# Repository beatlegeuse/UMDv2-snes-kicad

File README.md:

# UMDv2-snes-kicad
UMDv2 SNES Cartridge Adapter

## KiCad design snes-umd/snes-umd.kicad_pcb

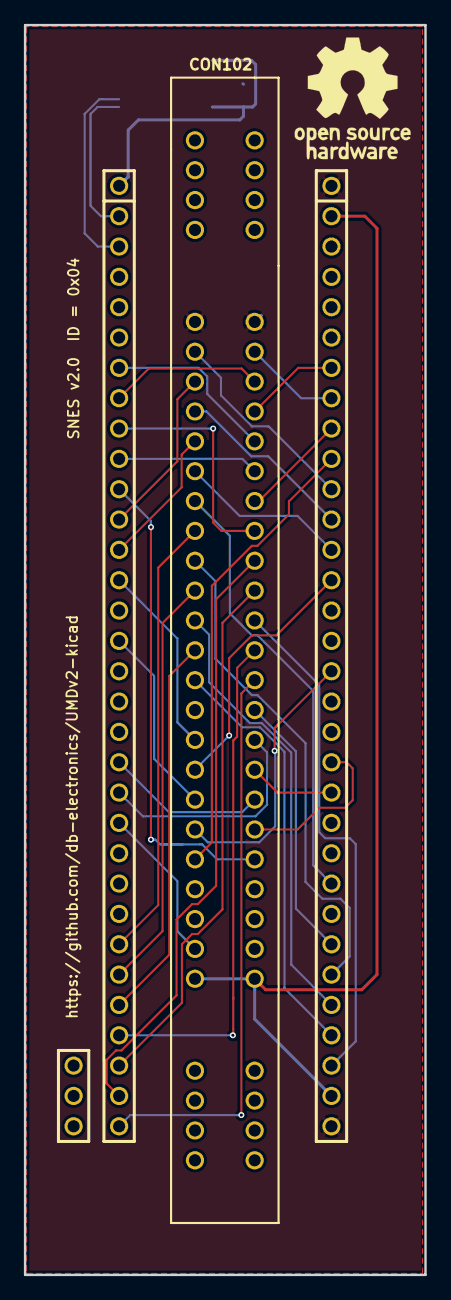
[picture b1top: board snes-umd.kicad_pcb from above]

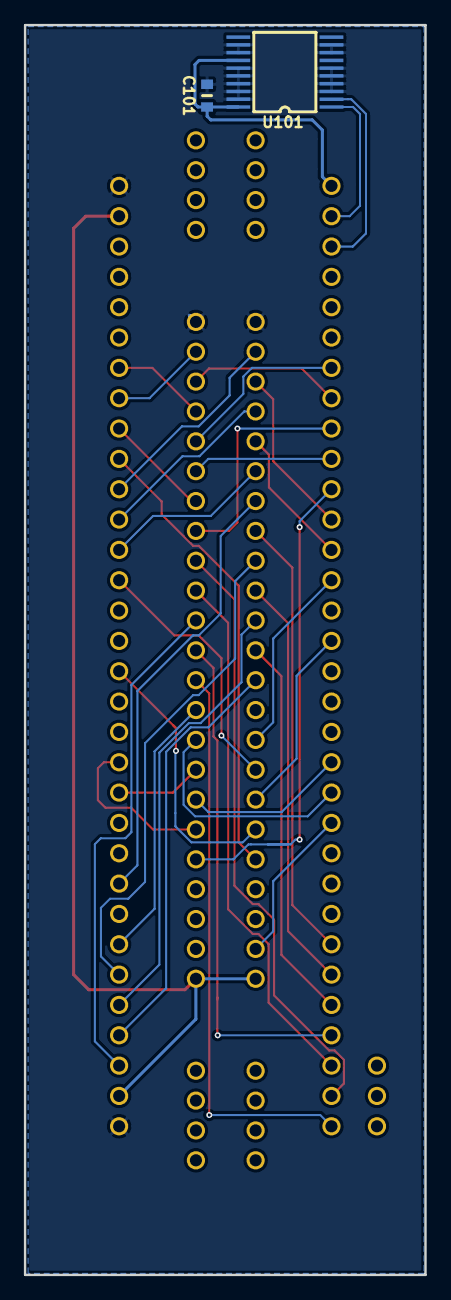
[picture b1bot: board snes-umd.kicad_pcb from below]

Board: 2 copper layers, 33.5 x 104.6 mm, 4 parts (2 on the bottom side), 41 nets.

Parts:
C101: 0.1uF/50V; 0603
CON101: UMDv2-CONN; UMD-CONN-DIP64
CON102: SNES-CONN; SNES-CONN-EXP
U101: MCP23008T-E_SS; SSOP-20

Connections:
+3V3: C101.1, CON101.1, U101.14, U101.20
+5V: CON101.34, CON101.63, CON102.27, CON102.58
/A0: CON101.36, CON102.17
/A1: CON101.28, CON102.16
/A2: CON101.37, CON102.15
/A3: CON101.27, CON102.14
/A4: CON101.38, CON102.13
/A5: CON101.26, CON102.12
/A6: CON101.41, CON102.11
/A7: CON101.52, CON102.10
/A8: CON101.13, CON102.9
/A9: CON101.53, CON102.8
/A10: CON101.12, CON102.7
/A11: CON101.54, CON102.6
/A12: CON101.57, CON102.37
/A13: CON101.8, CON102.38
/A14: CON101.58, CON102.39
/A15: CON101.7, CON102.40
/A16: CON101.10, CON102.41
/A17: CON101.56, CON102.42
/A18: CON101.9, CON102.43
/A19: CON101.31, CON102.44
/A20: CON101.30, CON102.45
/A21: CON101.35, CON102.46
/A22: CON101.29, CON102.47
/A23: CON101.32, CON102.48
/D0: CON101.14, CON102.19
/D1: CON101.51, CON102.20
/D2: CON101.16, CON102.21
/D3: CON101.48, CON102.22
/D4: CON101.21, CON102.50
/D5: CON101.44, CON102.51
/D6: CON101.20, CON102.52
/D7: CON101.45, CON102.53
/SCL: CON101.2, U101.1
/SDA: CON101.3, U101.2
/~CE: CON101.39, CON102.49
/~RD: CON101.55, CON102.23
/~RESET: CON101.22, CON102.26
/~WR: CON101.11, CON102.54
GND: C101.2, CON101.33, CON101.64, CON102.5, CON102.36, U101.3, U101.4, U101.5, U101.6, U101.8, U101.9, U101.12, U101.13, U101.15, U101.16, U101.17, U101.18, U101.19

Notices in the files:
snes-umd/snes-umd.kicad_pcb:
Licensed Under CERN OHL v.1.2
